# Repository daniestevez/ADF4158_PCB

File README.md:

# ADF4158 + HMC391 PCB

This project is a PCB that contains an
[ADF4158](https://www.analog.com/en/products/adf4158.html) direct
modulation/waveform generating fractional-N frequency synthesizer and a
[HMC391](https://www.analog.com/en/products/hmc391.html) 3.9 - 4.45 GHz VCO. The
board is primarily intended as an LO source for a 10 GHz FMCW radar inspired by
the
[ADALM-PHASER](https://wiki.analog.com/resources/eval/user-guides/circuits-from-the-lab/cn0566/overview_setup). The
VCO output can be used with a subharmonic mixer and an IF around 1.6 GHz to
cover the 10 - 10.5 GHz amateur radio band.

The board runs from a 12 - 16 VDC supply, exposes all the control pins of the
ADF4158 in a 2.58 mm pin header (3.3V logic) and includes an optional 10 MHz
reference input. The BOM cost is around 50€.

The PLL loop filter has been design with
[ADIsimPLL](https://www.analog.com/en/lp/resources/adisimpll.html). The design
file is [ADF4158_HMC391.pll](ADF4158_HMC391.pll).

## Outputs

Outputs for the latest commit in the `main` branch are built by CI and published
to Github pages. Additionally, outputs for each commit are published as a Github
artifact.

- [Schematic PDF](https://daniestevez.github.io/ADF4158_PCB/schematic.pdf)
- [PCB PDF](https://daniestevez.github.io/ADF4158_PCB/pcb.pdf)
- [Gerbers](https://daniestevez.github.io/ADF4158_PCB/gerbers.zip)
- [ERC report](https://daniestevez.github.io/ADF4158_PCB/erc.rpt)
- [DRC report](https://daniestevez.github.io/ADF4158_PCB/drc.rpt)
- [PCB top 3D render](https://daniestevez.github.io/ADF4158_PCB/pcb-top.png)
- [PCB bottom 3D render](https://daniestevez.github.io/ADF4158_PCB/pcb-bottom.png)

## BOM

The BOM for this project is available as a [DigiKey
list](https://www.digikey.es/en/mylists/list/1BEYR2RWXI). Note that this list
includes DNP components such as the SMA connector for the external 10 MHz
reference. You might want to exclude these components from your purchase.

## PCB fabrication

The PCB is intended to be fabricated on [JLCPCB](https://jlcpcb.com/) using the
following options:

- Base material: FR-4
- Layers: 4
- Deburring/Edge rounding: Yes
- PCB thickness: 1.6 mm
- Material type: FR4-Standard TG 135-140
- Surface finish: HASL (with lead)
- Outer copper weight: 1 oz
- Inner copper weight: 0.5 oz
- Specify stackup: yes
- Layer stackup: JLC04161H-7628 (50 ohm RF traces are designed for this stack up)
- Via covering: plugged
- Min via hole size/diamager: 0.3 mm (0.4/0.45 mm)

These options are very inexpensive: $7.10 for qty. 5, $13.20 for qty. 10.

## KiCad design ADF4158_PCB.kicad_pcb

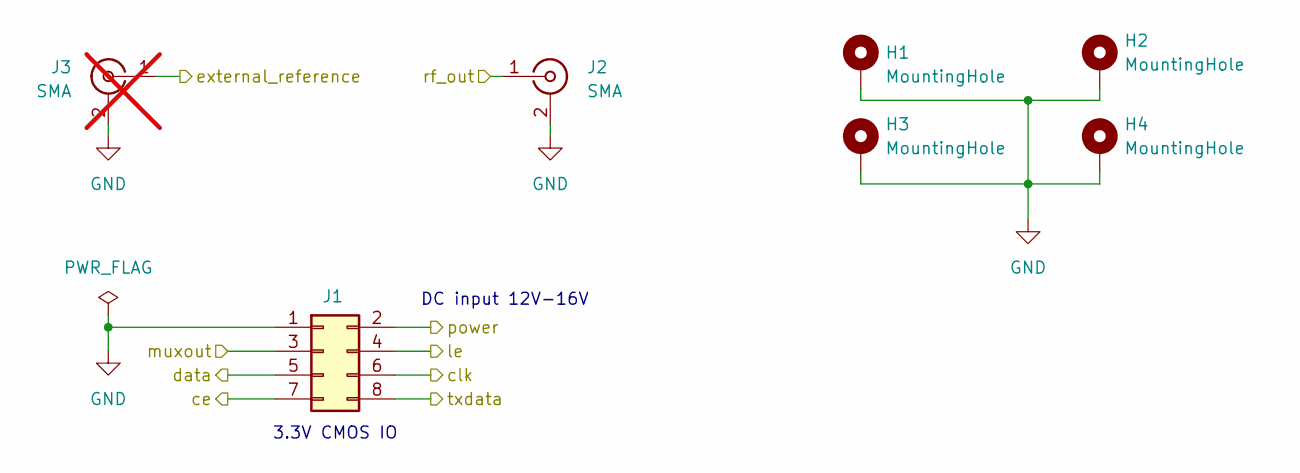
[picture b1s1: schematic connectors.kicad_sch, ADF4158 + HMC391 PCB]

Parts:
H1, H2, H3, H4: MountingHole; MountingHole_2.2mm_M2_Pad
J1: Conn_02x04_Odd_Even; PinHeader_2x04_P2.54mm_Vertical; Digikey Part Number 2057-PH2-08-UA-ND
J2: SMA; 2484637-1; Digikey Part Number 343-2484637-1-ND
J3: SMA; WRL-23187; Digikey Part Number 1568-WRL-23187-ND; not fitted

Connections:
/ADF4158 + HMC391/ce: J1.7; also elsewhere on the board
/ADF4158 + HMC391/clk: J1.6; also elsewhere on the board
/ADF4158 + HMC391/data: J1.5; also elsewhere on the board
/ADF4158 + HMC391/external_reference: J3.1 (In); also elsewhere on the board
/ADF4158 + HMC391/le: J1.4; also elsewhere on the board
/ADF4158 + HMC391/txdata: J1.8; also elsewhere on the board
/Connectors/power: J1.2; also elsewhere on the board
/muxout: J1.3; also elsewhere on the board
/rf_out: J2.1 (In); also elsewhere on the board
GND: H1.1, H2.1, H3.1, H4.1, J1.1, J2.2 (Ext), J3.2 (Ext); also elsewhere on the board

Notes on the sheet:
DC input 12V-16V
3.3V CMOS IO

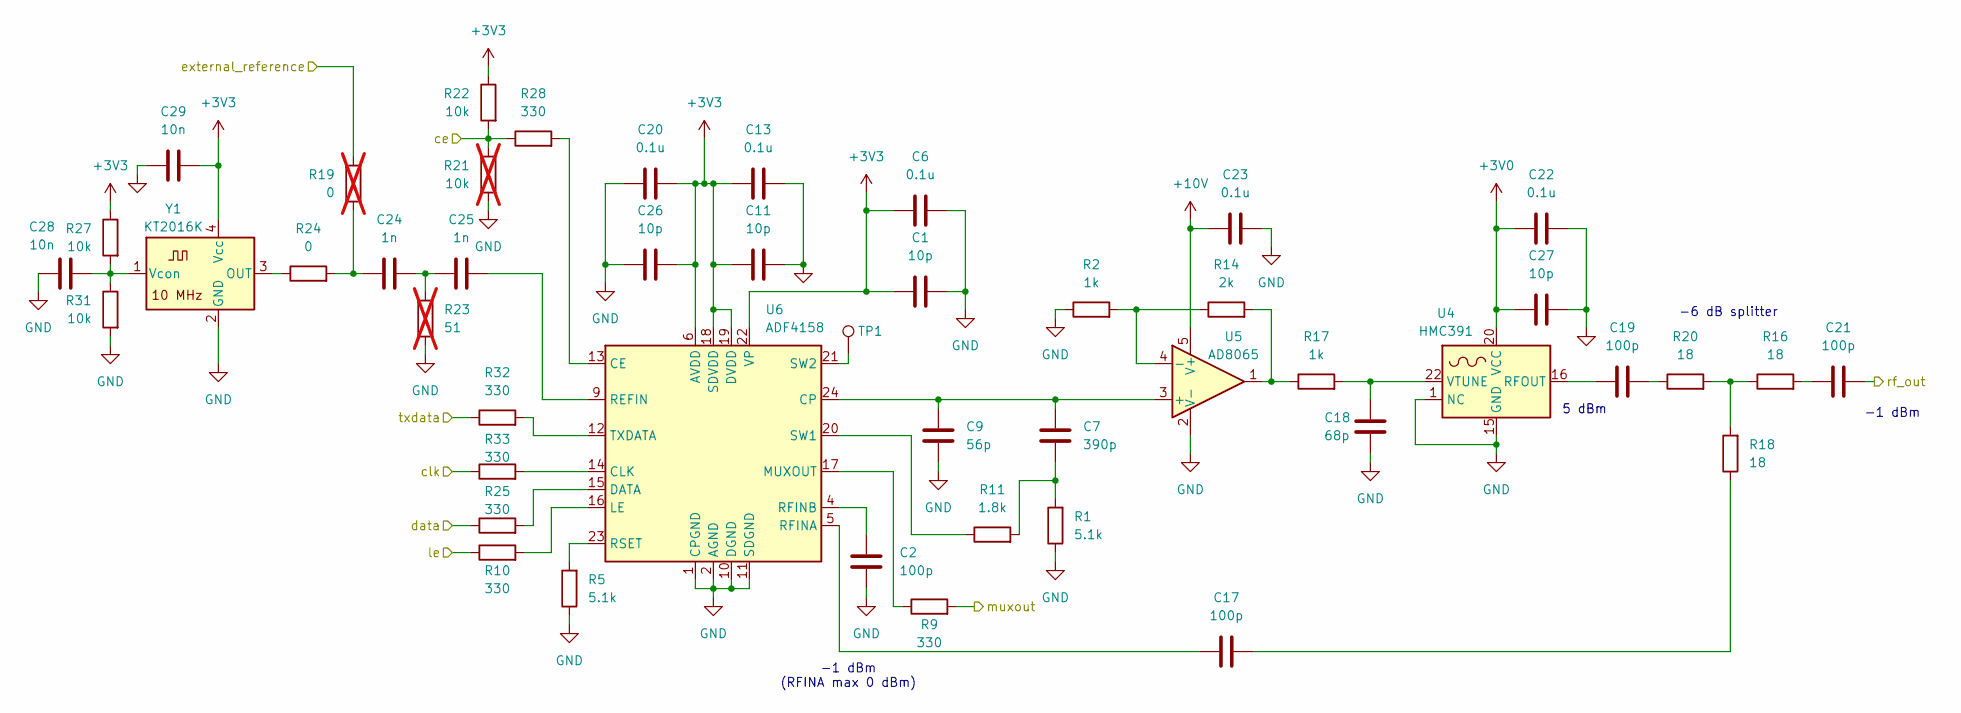
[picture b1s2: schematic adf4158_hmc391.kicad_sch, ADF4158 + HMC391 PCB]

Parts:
C1, C11, C26, C27: 10p; C_0402_1005Metric; Digikey Part Number 1276-1139-1-ND
C2, C17, C19, C21: 100p; C_0402_1005Metric; Digikey Part Number 1276-1025-1-ND
C6, C13, C20, C22, C23: 0.1u; C_0402_1005Metric; Digikey Part Number 1276-1002-1-ND
C7: 390p; C_0402_1005Metric; Digikey Part Number 490-1296-1-ND
C9: 56p; C_0402_1005Metric; Digikey Part Number 490-1288-1-ND
C18: 68p; C_0402_1005Metric; Digikey Part Number 490-5876-1-ND
C24, C25: 1n; C_0402_1005Metric; Digikey Part Number 1276-1032-1-ND
C28, C29: 10n; C_0402_1005Metric; Digikey Part Number 1276-1028-1-ND
R1, R5: 5.1k; R_0402_1005Metric; Digikey Part Number P5.1KDCCT-ND
R2, R17: 1k; R_0402_1005Metric; Digikey Part Number P1.00KLCT-ND
R9, R10, R25, R28, R32, R33: 330; R_0402_1005Metric; Digikey Part Number P330LCT-ND
R11: 1.8k; R_0402_1005Metric; Digikey Part Number P1.80KLCT-ND
R14: 2k; R_0402_1005Metric; Digikey Part Number P2.00KLCT-ND
R16, R18, R20: 18; R_0402_1005Metric; Digikey Part Number P18.0LCT-ND
R19: 0; R_0402_1005Metric; Digikey Part Number P0.0JCT-ND; not fitted
R21: 10k; R_0402_1005Metric; Digikey Part Number P10.0KLCT-ND; not fitted
R22, R27, R31: 10k; R_0402_1005Metric; Digikey Part Number P10.0KLCT-ND
R23: 51; R_0402_1005Metric; Digikey Part Number P51.0LCT-ND; not fitted
R24: 0; R_0402_1005Metric; Digikey Part Number P0.0JCT-ND
TP1: TestPoint; TestPoint_Pad_D2.0mm
U4: HMC391; QFN-24-1EP_4x4mm_P0.5mm_EP2.8x2.8mm; Digikey Part Number 505-HMC391LP4ECT-ND
U5: AD8065; TSOT-23-5; Digikey Part Number AD8065ARTZ-REELCT-ND
U6: ADF4158; LFCSP-24-1EP_4x4mm_P0.5mm_EP2.5x2.5mm; Digikey Part Number 505-ADF4158CCPZ-ND
Y1: KT2016K; Digikey Part Number 478-KT2016K10000ZAW33ZGKCT-ND

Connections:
+3V0: C22.2, C27.2, U4.20 (VCC); also elsewhere on the board
+3V3: C1.2, C6.2, C11.2, C13.2, C20.2, C26.2, C29.1, R22.1, R27.1, U6.6 (AVDD), U6.7 (AVDD), U6.8 (AVDD), U6.18 (SDVDD), U6.19 (DVDD), U6.22 (VP), Y1.4 (Vcc); also elsewhere on the board
+10V: C23.2, U5.5 (V+); also elsewhere on the board
/ADF4158 + HMC391/ce: R21.1, R22.2, R28.1; also elsewhere on the board
/ADF4158 + HMC391/clk: R33.1; also elsewhere on the board
/ADF4158 + HMC391/data: R25.1; also elsewhere on the board
/ADF4158 + HMC391/external_reference: R19.2; also elsewhere on the board
/ADF4158 + HMC391/le: R10.1; also elsewhere on the board
/ADF4158 + HMC391/txdata: R32.1; also elsewhere on the board
/muxout: R9.2; also elsewhere on the board
/rf_out: C21.2; also elsewhere on the board
GND: C1.1, C2.2, C6.1, C9.2, C11.1, C13.1, C18.2, C20.1, C22.1, C23.1, C26.1, C27.1, C28.1, C29.2, R1.1, R2.1, R5.1, R21.2, R23.1, R31.2, U4.1 (NC), U4.2 (NC), U4.3 (NC), U4.4 (NC), U4.5 (NC), U4.6 (NC), U4.7 (NC), U4.8 (NC), U4.9 (NC), U4.10 (NC), U4.11 (NC), U4.12 (NC), U4.13 (NC), U4.14 (NC), U4.15 (GND), U4.17 (NC), U4.18 (NC), U4.19 (NC), U4.21 (NC), U4.23 (NC), U4.24 (NC), U4.25 (GND), U5.2 (V-), U6.1 (CPGND), U6.2 (AGND), U6.3 (AGND), U6.10 (DGND), U6.11 (SDGND), U6.25 (AGND), Y1.2 (GND); also elsewhere on the board
unnamed: C7.2, R1.2, R11.2
unnamed: C17.2, R18.1
unnamed: C19.2, R20.1
unnamed: C21.1, R16.2
unnamed: C24.1, R19.1, R24.2
unnamed: C24.2, C25.1, R23.2
unnamed: R14.2, R17.1, U5.1
unnamed: R16.1, R18.2, R20.2
unnamed: C19.1, U4.16 (RFOUT)
unnamed: C18.1, R17.2, U4.22 (VTUNE)
unnamed: C7.1, C9.1, U5.3 (+), U6.24 (CP)
unnamed: R2.2, R14.1, U5.4 (-)
unnamed: R28.2, U6.13 (CE)
unnamed: R33.2, U6.14 (CLK)
unnamed: R25.2, U6.15 (DATA)
unnamed: R10.2, U6.16 (LE)
unnamed: R9.1, U6.17 (MUXOUT)
unnamed: C25.2, U6.9 (REFIN)
unnamed: C17.1, U6.5 (RFINA)
unnamed: C2.1, U6.4 (RFINB)
unnamed: R5.2, U6.23 (RSET)
unnamed: R11.1, U6.20 (SW1)
unnamed: TP1.1, U6.21 (SW2)
unnamed: R32.2, U6.12 (TXDATA)
unnamed: R24.1, Y1.3 (OUT)
unnamed: C28.2, R27.2, R31.1, Y1.1 (Vcon)

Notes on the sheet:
-6 dB splitter
-1 dBm (RFINA max 0 dBm)
-1 dBm
5 dBm

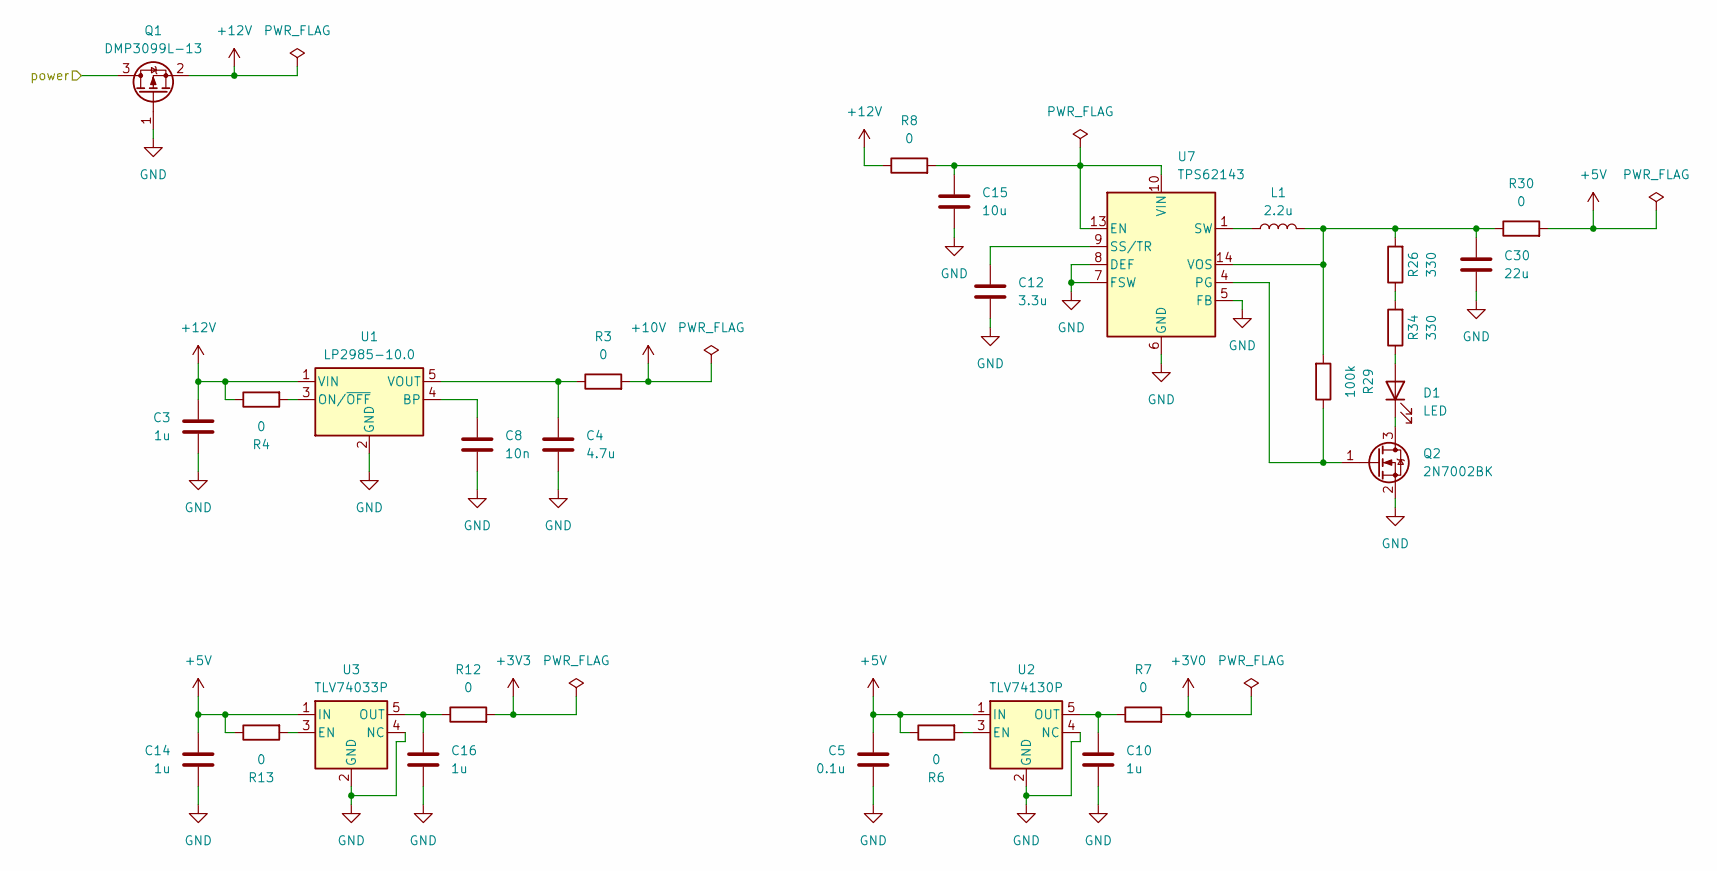
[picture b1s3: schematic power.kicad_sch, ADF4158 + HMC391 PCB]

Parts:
C3, C10, C14, C16: 1u; C_0603_1608Metric; Digikey Part Number 1276-1184-1-ND
C4: 4.7u; C_0805_2012Metric; Digikey Part Number 490-GRM21BR71C475ME51KCT-ND
C5: 0.1u; C_0402_1005Metric; Digikey Part Number 1276-1002-1-ND
C8: 10n; C_0402_1005Metric; Digikey Part Number 1276-1028-1-ND
C12: 3.3u; C_1206_3216Metric; Digikey Part Number 1276-1841-1-ND
C15: 10u; C_0805_2012Metric; Digikey Part Number 1276-2872-1-ND
C30: 22u; C_0603_1608Metric; Digikey Part Number 1276-1274-1-ND
D1: LED; LED_0603_1608Metric; Digikey Part Number 3147-B1931NG--20D001114U1930CT-ND
L1: 2.2u; L_1008_2520Metric; Digikey Part Number 490-10649-1-ND
Q1: DMP3099L-13; SOT-23-3; Digikey Part Number DMP3099L-13DICT-ND
Q2: 2N7002BK; SOT-23; Digikey Part Number 1727-4789-1-ND
R3, R4, R6, R7, R8, R12, R13, R30: 0; R_0402_1005Metric; Digikey Part Number P0.0JCT-ND
R26, R34: 330; R_0402_1005Metric; Digikey Part Number P330LCT-ND
R29: 100k; R_0402_1005Metric; Digikey Part Number P100KLCT-ND
U1: LP2985-10.0; SOT-23-5; Digikey Part Number 296-24263-1-ND
U2: TLV74130P; SOT-23-5; Digikey Part Number 296-50000-1-ND
U3: TLV74033P; SOT-23-5; Digikey Part Number 296-TLV74033PDBVRCT-ND
U7: TPS62143; VQFN-16-1EP_3x3mm_P0.5mm_EP1.68x1.68mm; Digikey Part Number 296-39448-1-ND

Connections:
+3V0: R7.2; also elsewhere on the board
+3V3: R12.2; also elsewhere on the board
+5V: C5.1, C14.1, R6.1, R13.1, R30.2, U2.1 (IN), U3.1 (IN)
+10V: R3.2; also elsewhere on the board
+12V: C3.1, Q1.2 (S), R4.1, R8.1, U1.1 (VIN)
/Connectors/power: Q1.3 (D); also elsewhere on the board
GND: C3.2, C4.2, C5.2, C8.2, C10.2, C12.2, C14.2, C15.2, C16.2, C30.2, Q1.1 (G), Q2.2 (S), U1.2 (GND), U2.2 (GND), U2.4 (NC), U3.2 (GND), U3.4 (NC), U7.5 (FB), U7.6 (GND), U7.7 (FSW), U7.8 (DEF), U7.15 (GND), U7.16 (GND), U7.17 (GND); also elsewhere on the board
unnamed: D1.2 (A), R34.1
unnamed: D1.1 (K), Q2.3 (D)
unnamed: L1.1, U7.1 (SW), U7.2 (SW), U7.3 (SW)
unnamed: Q2.1 (G), R29.1, U7.4 (PG)
unnamed: R26.1, R34.2
unnamed: C8.1, U1.4 (BP)
unnamed: R4.2, U1.3 (ON/~OFF)
unnamed: C4.1, R3.1, U1.5 (VOUT)
unnamed: R6.2, U2.3 (EN)
unnamed: C10.1, R7.1, U2.5 (OUT)
unnamed: R13.2, U3.3 (EN)
unnamed: C16.1, R12.1, U3.5 (OUT)
unnamed: C15.1, R8.2, U7.10 (VIN), U7.11 (VIN), U7.12 (VIN), U7.13 (EN)
unnamed: C12.1, U7.9 (SS/TR)
unnamed: C30.1, L1.2, R26.2, R29.2, R30.1, U7.14 (VOS)

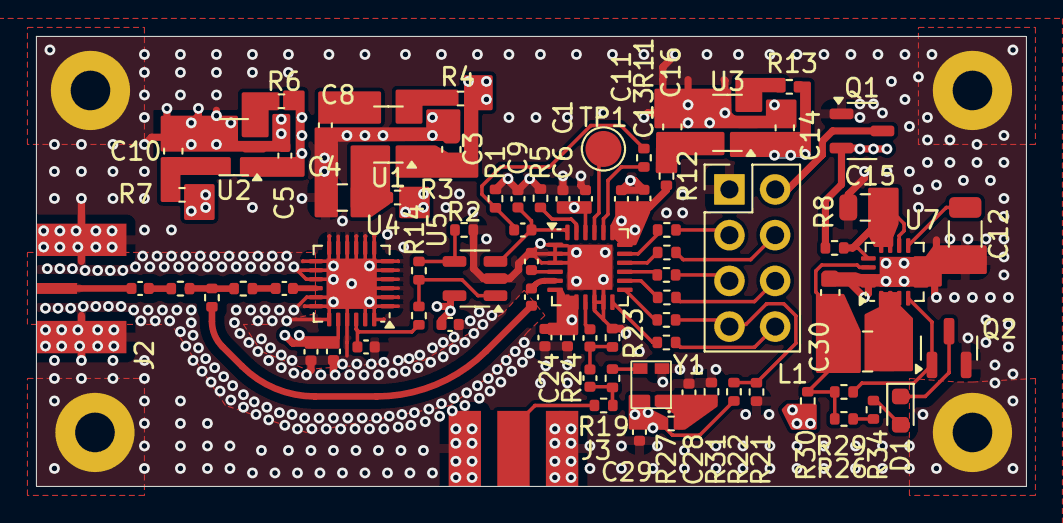
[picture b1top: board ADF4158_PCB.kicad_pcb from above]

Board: 4 copper layers, 55.0 x 25.0 mm, 83 parts (0 on the bottom side), 56 nets.

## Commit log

2025-04-12 add CI workflow
2025-04-12 update README
    Add links to Github pages and fabrication information.
2025-04-12 increase PCB render zoom
    Increase PCB render zoom to remove larger margin in the PNG file.
2025-04-12 add link to DigiKey list
2025-04-12 add PLL loop filter design file
2025-04-12 some minor PCB improvements
    - Do not route 3V0 trace on back right below HMC391 RF out
    - Add multiple vias for 5V and 12V power traces
2025-04-20 switch to 4-layer 1.6mm PCB stackup from JLCPCB
    - By recommendation of reviewers, use a 4-layer 1.6 PCB stackup from
    JLCPCB that gives 0.6 mm 50 ohm CPWG traces on the top layer.
    - Use an SMA connector with a thin pin for the RF output.
    - Remove 51 ohm resistor loading the ADF4518 PCB. This is believed
    to be a mistake in the evaluation board schematic.
    - Add M2 mounting holes to the board corners.
2025-04-20 switch from JLC04161H-2116D to JLC04161H-7628 stackup
    Unfortunately the 2116D stackup that I used to get 50 ohm traces
    of approximately 0.6 mm now costs a huge amount. Use instead the
    7628 stackup, which is JLCPCB's cheap/default/recommended stackup.
    This gives 0.3658 mm 50 ohm traces, which is not ideal for matching
    with 0402 parts.
2025-04-20 use thermal relief in GND pour
    - Use thermal relief in GND pour
    - Add vias to SMD GND pads
2025-04-22 add plating to mounting holes
2025-04-22 replace U7 footprint vias by manually placed vias
    The thermal vias in the footprint were being connected
    to the groundplane with thermal reliefs and giving other
    troubles (wrong drill size). This replaces them by manually
    placed vias.
2025-04-25 add release dates to schematic and PCB
2025-09-04 update footprints from library
    Update footprints from library to fix DRC warnings, since the library
    has now been updated.
2025-09-04 add assembled PCB photo
2025-09-04 fix typo in README
